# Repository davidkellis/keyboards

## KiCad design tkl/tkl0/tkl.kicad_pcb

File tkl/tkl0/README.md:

# TKL v0: original KiCad project

This is the original keyboard project that preceded the later numbered design
iterations. Its PCB, schematic, and project files are preserved byte for byte.

- Open [tkl.kicad_pro](tkl.kicad_pro) in KiCad.
- [PCB](tkl.kicad_pcb)
- [Schematic](tkl.kicad_sch)

The KiCad project is still named `tkl`; the directory name identifies this
snapshot as v0. See the [repository index](../../README.md) for later revisions.

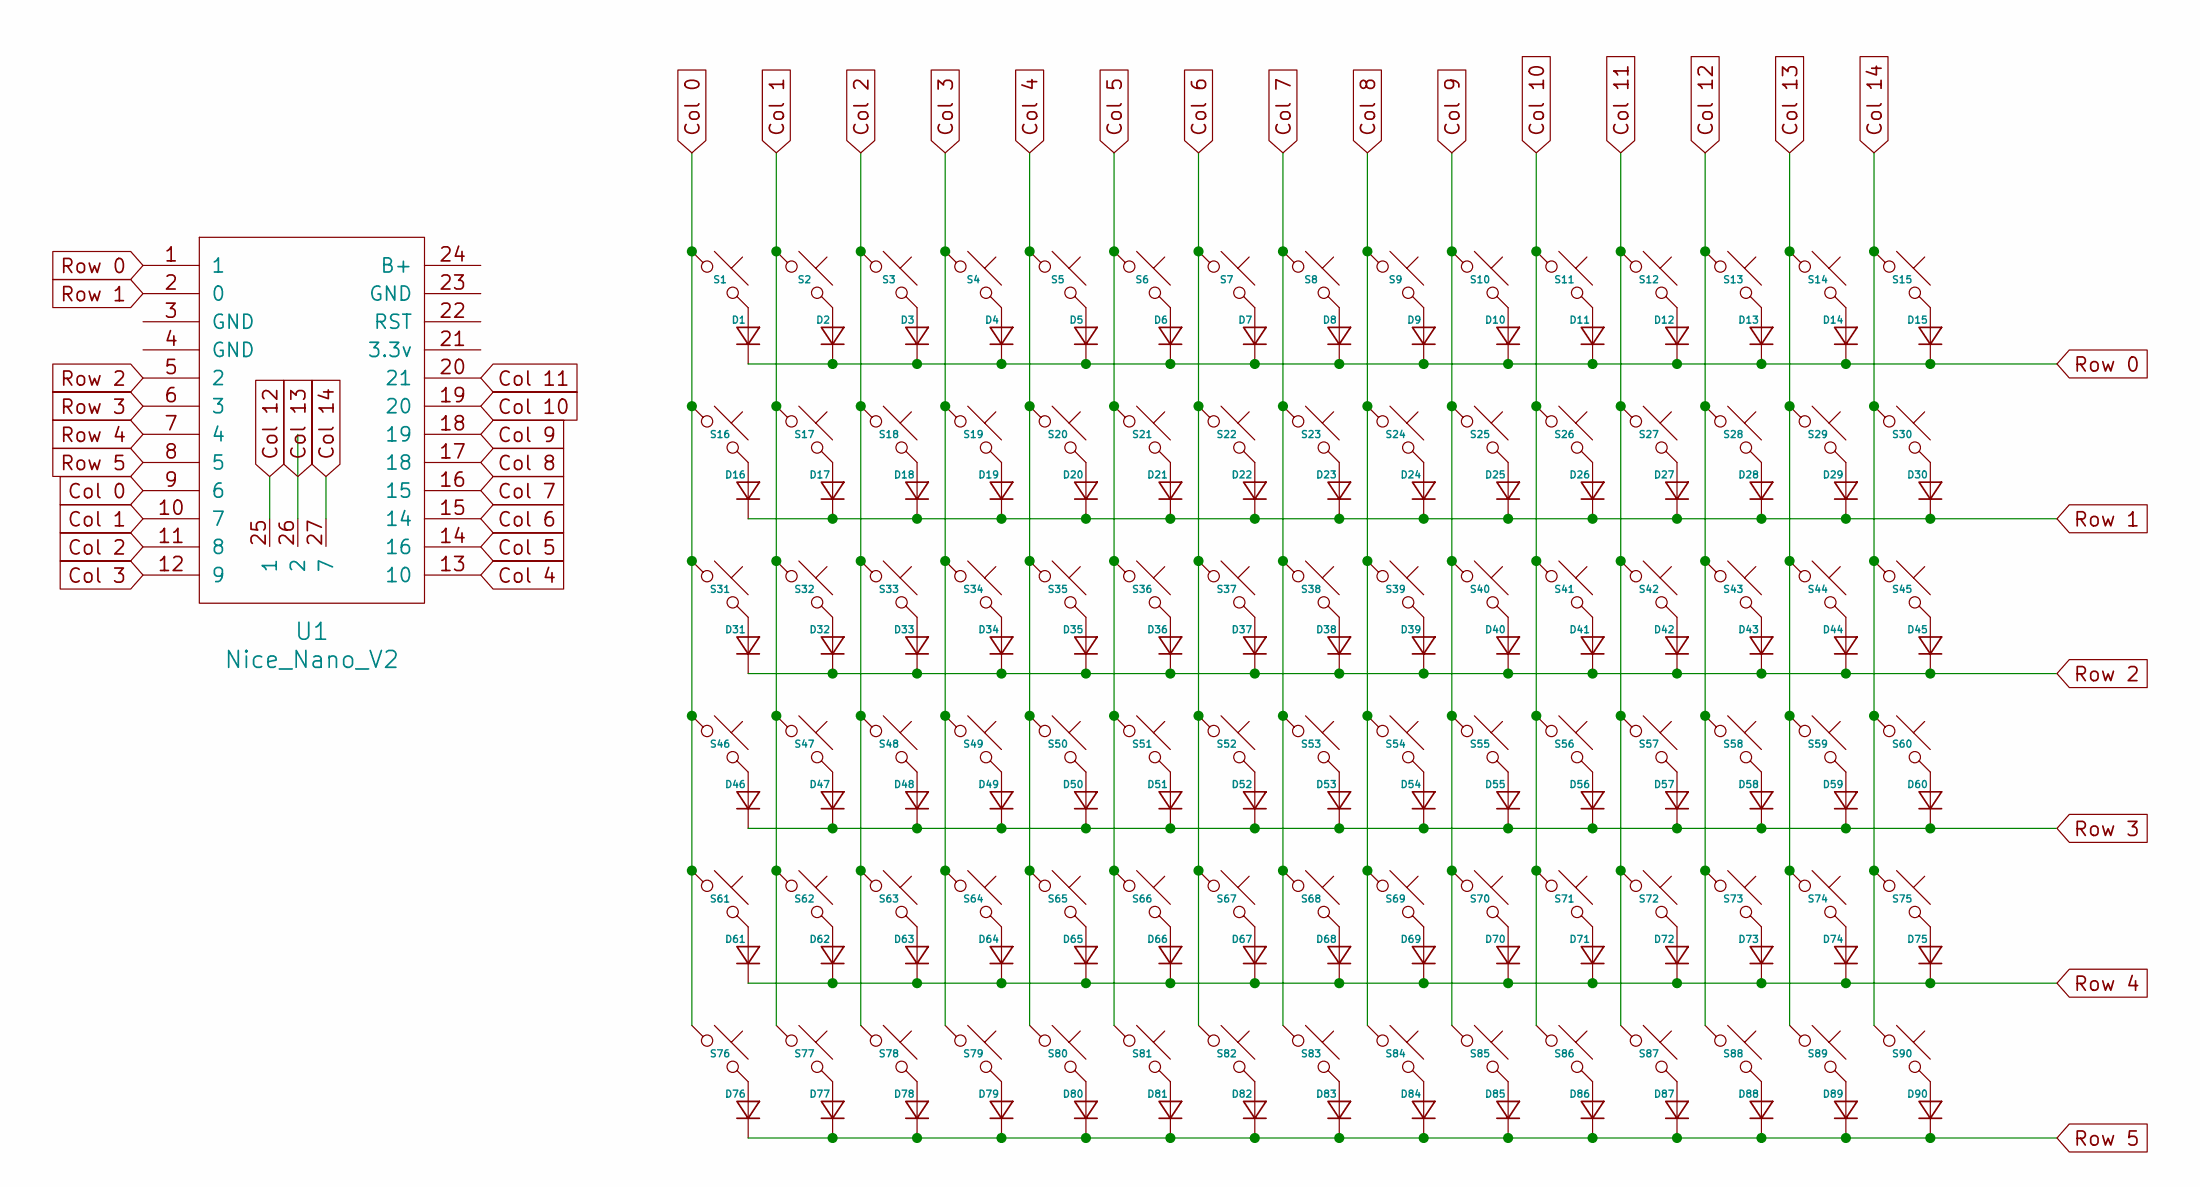
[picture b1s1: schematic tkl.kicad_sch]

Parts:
D1, D2, D3, D4, D5, D6, D7, D8, D9, D10, D11, D12, D13, D14, D15, D16, D17, D18, D19, D20, D21, D22, D23, D24, D25, D26, D27, D28, D29, D30, D31, D32, D33, D34, D35, D36, D37, D38, D39, D40, D41, D42, D43, D44, D45, D46, D47, D48, D49, D50, D51, D52, D53, D54, D55, D56, D57, D58, D59, D60, D61, D62, D63, D64, D65, D66, D67, D68, D69, D70, D71, D72, D73, D74, D75, D76, D77, D78, D79, D80, D81, D82, D83, D84, D85, D86, D87, D88, D89, D90: Diode_DO-35
S1, S2, S3, S4, S5, S6, S7, S8, S9, S10, S11, S12, S13, S14, S15, S16, S17, S18, S19, S20, S21, S22, S23, S24, S25, S26, S27, S28, S29, S30, S31, S32, S33, S34, S35, S36, S37, S38, S39, S40, S41, S42, S43, S44, S45, S46, S47, S48, S49, S50, S51, S52, S53, S54, S55, S56, S57, S58, S59, S60, S61, S62, S63, S64, S65, S66, S67, S68, S69, S70, S71, S72, S73, S74, S75, S76, S77, S78, S79, S80, S81, S82, S83, S84, S85, S86, S87, S88, S89, S90: Choc_V2_1.00u
U1: Nice_Nano_V2

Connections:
Col 0: S1.1, S16.1, S31.1, S46.1, S61.1, S76.1, U1.9 (6)
Col 1: S2.1, S17.1, S32.1, S47.1, S62.1, S77.1, U1.10 (7)
Col 2: S3.1, S18.1, S33.1, S48.1, S63.1, S78.1, U1.11 (8)
Col 3: S4.1, S19.1, S34.1, S49.1, S64.1, S79.1, U1.12 (9)
Col 4: S5.1, S20.1, S35.1, S50.1, S65.1, S80.1, U1.13 (10)
Col 5: S6.1, S21.1, S36.1, S51.1, S66.1, S81.1, U1.14 (16)
Col 6: S7.1, S22.1, S37.1, S52.1, S67.1, S82.1, U1.15 (14)
Col 7: S8.1, S23.1, S38.1, S53.1, S68.1, S83.1, U1.16 (15)
Col 8: S9.1, S24.1, S39.1, S54.1, S69.1, S84.1, U1.17 (18)
Col 9: S10.1, S25.1, S40.1, S55.1, S70.1, S85.1, U1.18 (19)
Col 10: S11.1, S26.1, S41.1, S56.1, S71.1, S86.1, U1.19 (20)
Col 11: S12.1, S27.1, S42.1, S57.1, S72.1, S87.1, U1.20 (21)
Col 12: S13.1, S28.1, S43.1, S58.1, S73.1, S88.1, U1.25 (1)
Col 13: S14.1, S29.1, S44.1, S59.1, S74.1, S89.1, U1.26 (2)
Col 14: S15.1, S30.1, S45.1, S60.1, S75.1, S90.1, U1.27 (7)
unnamed: D1.2 (A), S1.2
unnamed: D2.2 (A), S2.2
unnamed: D3.2 (A), S3.2
unnamed: D4.2 (A), S4.2
unnamed: D5.2 (A), S5.2
unnamed: D6.2 (A), S6.2
unnamed: D7.2 (A), S7.2
unnamed: D8.2 (A), S8.2
unnamed: D9.2 (A), S9.2
unnamed: D10.2 (A), S10.2
unnamed: D11.2 (A), S11.2
unnamed: D12.2 (A), S12.2
unnamed: D13.2 (A), S13.2
unnamed: D14.2 (A), S14.2
unnamed: D15.2 (A), S15.2
unnamed: D16.2 (A), S16.2
unnamed: D17.2 (A), S17.2
unnamed: D18.2 (A), S18.2
unnamed: D19.2 (A), S19.2
unnamed: D20.2 (A), S20.2
unnamed: D21.2 (A), S21.2
unnamed: D22.2 (A), S22.2
unnamed: D23.2 (A), S23.2
unnamed: D24.2 (A), S24.2
unnamed: D25.2 (A), S25.2
unnamed: D26.2 (A), S26.2
unnamed: D27.2 (A), S27.2
unnamed: D28.2 (A), S28.2
unnamed: D29.2 (A), S29.2
unnamed: D30.2 (A), S30.2
unnamed: D31.2 (A), S31.2
unnamed: D32.2 (A), S32.2
unnamed: D33.2 (A), S33.2
unnamed: D34.2 (A), S34.2
unnamed: D35.2 (A), S35.2
unnamed: D36.2 (A), S36.2
unnamed: D37.2 (A), S37.2
unnamed: D38.2 (A), S38.2
unnamed: D39.2 (A), S39.2
unnamed: D40.2 (A), S40.2
unnamed: D41.2 (A), S41.2
unnamed: D42.2 (A), S42.2
unnamed: D43.2 (A), S43.2
unnamed: D44.2 (A), S44.2
unnamed: D45.2 (A), S45.2
unnamed: D46.2 (A), S46.2
unnamed: D47.2 (A), S47.2
unnamed: D48.2 (A), S48.2
unnamed: D49.2 (A), S49.2
unnamed: D50.2 (A), S50.2
unnamed: D51.2 (A), S51.2
unnamed: D52.2 (A), S52.2
unnamed: D53.2 (A), S53.2
unnamed: D54.2 (A), S54.2
unnamed: D55.2 (A), S55.2
unnamed: D56.2 (A), S56.2
unnamed: D57.2 (A), S57.2
unnamed: D58.2 (A), S58.2
unnamed: D59.2 (A), S59.2
unnamed: D60.2 (A), S60.2
unnamed: D61.2 (A), S61.2
unnamed: D62.2 (A), S62.2
unnamed: D63.2 (A), S63.2
unnamed: D64.2 (A), S64.2
unnamed: D65.2 (A), S65.2
unnamed: D66.2 (A), S66.2
unnamed: D67.2 (A), S67.2
unnamed: D68.2 (A), S68.2
unnamed: D69.2 (A), S69.2
unnamed: D70.2 (A), S70.2
unnamed: D71.2 (A), S71.2
unnamed: D72.2 (A), S72.2
unnamed: D73.2 (A), S73.2
unnamed: D74.2 (A), S74.2
unnamed: D75.2 (A), S75.2
unnamed: D76.2 (A), S76.2
unnamed: D77.2 (A), S77.2
unnamed: D78.2 (A), S78.2
unnamed: D79.2 (A), S79.2
unnamed: D80.2 (A), S80.2
unnamed: D81.2 (A), S81.2
unnamed: D82.2 (A), S82.2
unnamed: D83.2 (A), S83.2
unnamed: D84.2 (A), S84.2
unnamed: D85.2 (A), S85.2
unnamed: D86.2 (A), S86.2
unnamed: D87.2 (A), S87.2
unnamed: D88.2 (A), S88.2
unnamed: D89.2 (A), S89.2
unnamed: D90.2 (A), S90.2
Row 0: D1.1 (K), D2.1 (K), D3.1 (K), D4.1 (K), D5.1 (K), D6.1 (K), D7.1 (K), D8.1 (K), D9.1 (K), D10.1 (K), D11.1 (K), D12.1 (K), D13.1 (K), D14.1 (K), D15.1 (K), U1.1
Row 1: D16.1 (K), D17.1 (K), D18.1 (K), D19.1 (K), D20.1 (K), D21.1 (K), D22.1 (K), D23.1 (K), D24.1 (K), D25.1 (K), D26.1 (K), D27.1 (K), D28.1 (K), D29.1 (K), D30.1 (K), U1.2 (0)
Row 2: D31.1 (K), D32.1 (K), D33.1 (K), D34.1 (K), D35.1 (K), D36.1 (K), D37.1 (K), D38.1 (K), D39.1 (K), D40.1 (K), D41.1 (K), D42.1 (K), D43.1 (K), D44.1 (K), D45.1 (K), U1.5 (2)
Row 3: D46.1 (K), D47.1 (K), D48.1 (K), D49.1 (K), D50.1 (K), D51.1 (K), D52.1 (K), D53.1 (K), D54.1 (K), D55.1 (K), D56.1 (K), D57.1 (K), D58.1 (K), D59.1 (K), D60.1 (K), U1.6 (3)
Row 4: D61.1 (K), D62.1 (K), D63.1 (K), D64.1 (K), D65.1 (K), D66.1 (K), D67.1 (K), D68.1 (K), D69.1 (K), D70.1 (K), D71.1 (K), D72.1 (K), D73.1 (K), D74.1 (K), D75.1 (K), U1.7 (4)
Row 5: D76.1 (K), D77.1 (K), D78.1 (K), D79.1 (K), D80.1 (K), D81.1 (K), D82.1 (K), D83.1 (K), D84.1 (K), D85.1 (K), D86.1 (K), D87.1 (K), D88.1 (K), D89.1 (K), D90.1 (K), U1.8 (5)

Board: 2 copper layers, 181 parts (0 on the bottom side), 111 nets, no tracks yet.

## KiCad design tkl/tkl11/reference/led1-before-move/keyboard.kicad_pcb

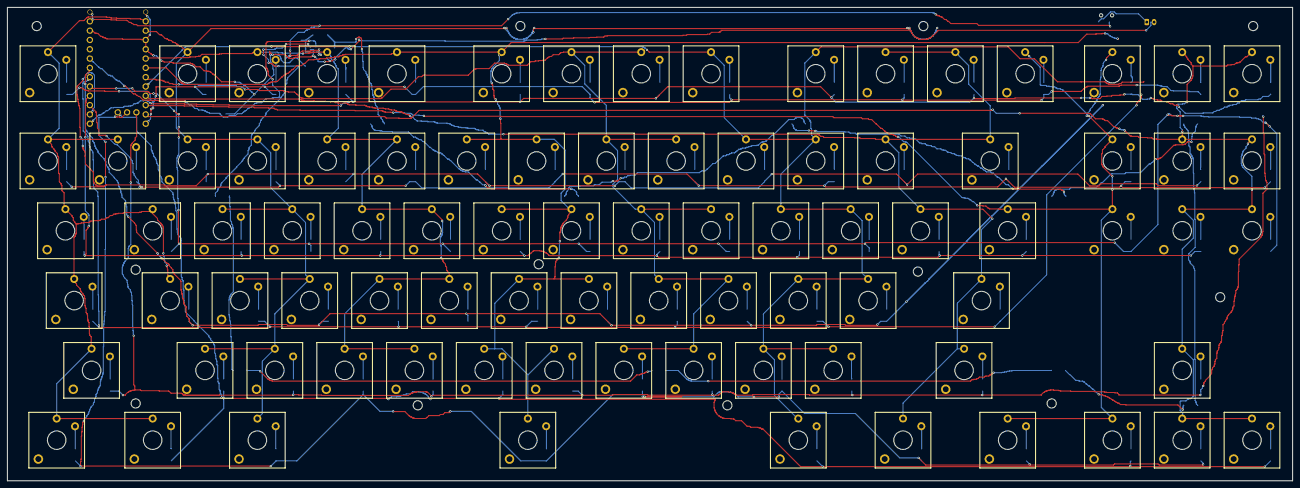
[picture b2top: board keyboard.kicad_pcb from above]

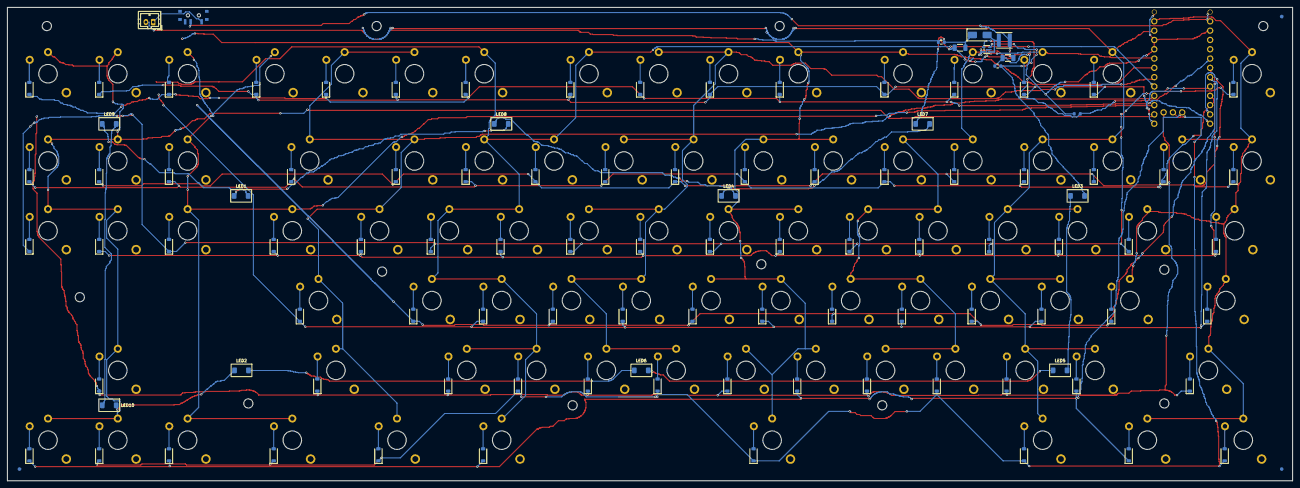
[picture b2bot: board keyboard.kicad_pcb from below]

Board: 2 copper layers, 350.8 x 129.2 mm, 208 parts (110 on the bottom side), 122 nets.

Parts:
C1, C2: 4.7uF 50V; C_1206_3216Metric
D1, D2, D3, D4, D5, D6, D7, D8, D9, D10, D11, D12, D13, D14, D15, D16, D17, D18, D19, D20, D21, D22, D23, D24, D25, D26, D27, D28, D29, D30, D31, D32, D33, D34, D35, D36, D37, D38, D39, D40, D41, D42, D43, D44, D45, D46, D47, D48, D49, D50, D51, D52, D53, D54, D55, D56, D57, D58, D59, D60, D61, D62, D63, D64, D65, D66, D67, D68, D69, D70, D71, D72, D73, D74, D75, D76, D77, D78, D79, D80, D81, D82, D83, D84, D85, D86: BAT46W; D_SOD-123
D87: SS16; D_SMA
FID1, FID2, FID3: Fiducial; Fiducial_1mm_Mask2mm
H1, H2, H3, H4, H5, H6, H7, H8, H9, H10, H11, H12: Mount_M2_2.5mm
J1: B2B-PH-K-S(LF)(SN); J1_JST_PH_B2B-PH-K_1x02_P2.00mm_Vertical
L1: 10uH; L_Sunlord_SWPA4018S
LED1, LED7, LED8, LED9, LED10: LTW-C230DS; LED1_LTW-C230DS_ReverseMount_Hole2.1x2.8
LED2: LTW-C230DS; LED2_LTW-C230DS_ReverseMount_Hole2.1x2.8
LED3: LTW-C230DS; LED3_LTW-C230DS_ReverseMount_Hole2.1x2.8
LED4: LTW-C230DS; LED4_LTW-C230DS_ReverseMount_Hole2.1x2.8
LED5: LTW-C230DS; LED5_LTW-C230DS_ReverseMount_Hole2.1x2.8
LED6: LTW-C230DS; LED6_LTW-C230DS_ReverseMount_Hole2.1x2.8
R9: 1M; R9_R_0603
R10: 100; R_0603_1608Metric
R11: 1M; R_0603_1608Metric
SW1, SW2, SW3, SW4, SW5, SW6, SW7, SW8, SW9, SW10, SW11, SW12, SW13, SW14, SW15, SW16, SW17, SW18, SW19, SW20, SW21, SW22, SW23, SW24, SW25, SW26, SW27, SW28, SW29, SW30, SW32, SW33, SW35, SW36, SW37, SW38, SW39, SW40, SW43, SW44, SW45, SW46, SW47, SW48, SW52, SW53, SW54, SW55, SW56, SW58, SW59, SW60, SW61, SW62, SW63, SW65, SW66, SW67, SW68, SW69, SW71, SW72, SW73, SW74, SW75, SW76, SW82, SW85, SW86: SW_Push; SW_Kailh_Choc_V2_1.00u
SW31: SW_Push; SW_Kailh_Choc_V2_2.00u
SW34, SW41, SW78, SW80, SW81, SW83, SW84: SW_Push; SW_Kailh_Choc_V2_1.50u
SW42: SW_Push; SW42_SW_Kailh_Choc_V2_1.00u
SW49: SW_Push; SW49_SW_Kailh_Choc_V2_1.00u
SW50: SW_Push; SW50_SW_Kailh_Choc_V2_1.00u
SW51: SW_Push; SW_Kailh_Choc_V2_1.75u
SW57, SW64: SW_Push; SW_Kailh_Choc_V2_2.25u
SW70: SW_Push; SW_Kailh_Choc_V2_2.75u
SW77: SW_Push; SW_Kailh_Choc_V2_1.25u
SW79: SW_Push; SW_Kailh_Choc_V2_6.25u
SW87: PCM12SMTR; SW87_SW_SPDT_PCM12
U1: Nice_Nano_V2; U1_Nice_Nano_V2
U2: TPS61169DCKR; SOT-353_SC-70-5

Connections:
BAT_SW: C1.1, L1.1, SW87.2, U1.24 (B+), U1.29 (B+), U2.5
BL_EN: R9.1, U1.20 (21), U2.4
BOOST_SW: D87.2, L1.2, U2.1
COL0: SW1.1, SW17.1, SW25.1, SW34.1, SW43.1, SW51.1, SW58.1, SW64.1, SW77.1, SW83.1, U1.1
COL1: SW2.1, SW18.1, SW26.1, SW35.1, SW44.1, SW52.1, SW59.1, SW65.1, SW71.1, SW78.1, U1.2 (0)
COL2: SW3.1, SW10.1, SW19.1, SW27.1, SW36.1, SW45.1, SW53.1, SW60.1, SW66.1, SW72.1, U1.5 (2)
COL3: SW4.1, SW11.1, SW20.1, SW28.1, SW37.1, SW46.1, SW54.1, SW61.1, SW67.1, SW73.1, SW79.1, U1.6 (3)
COL4: SW5.1, SW12.1, SW21.1, SW29.1, SW38.1, SW47.1, SW55.1, SW62.1, SW68.1, SW74.1, U1.7 (4)
COL5: SW6.1, SW13.1, SW22.1, SW30.1, SW39.1, SW48.1, SW56.1, SW63.1, SW69.1, SW75.1, SW84.1, U1.8 (5)
COL6: SW7.1, SW14.1, SW23.1, SW31.1, SW40.1, SW57.1, SW70.1, SW80.1, U1.9 (6)
COL7: SW8.1, SW15.1, SW32.1, SW41.1, SW49.1, SW81.1, SW85.1, U1.10 (7)
COL8: SW9.1, SW16.1, SW24.1, SW33.1, SW42.1, SW50.1, SW76.1, SW82.1, SW86.1, U1.11 (8)
GND: C1.2, C2.2, J1.2, R9.2, R10.2, R11.2, U1.3 (GND), U1.4 (GND), U1.23 (GND), U1.28 (B-), U2.2
LED_FB: LED3.1, R10.1, U2.3
LED_HV: C2.1, D87.1, LED7.2, R11.1
LED_LINK_1: LED4.2, LED7.1
LED_LINK_2: LED4.1, LED8.2
LED_LINK_3: LED1.2, LED8.1
LED_LINK_4: LED1.1, LED9.2
LED_LINK_5: LED9.1, LED10.2
LED_LINK_6: LED2.2, LED10.1
LED_LINK_7: LED2.1, LED6.2
LED_LINK_8: LED5.2, LED6.1
LED_LINK_9: LED3.2, LED5.1
unnamed: D1.2, SW1.2
unnamed: D2.2, SW2.2
unnamed: D3.2, SW3.2
unnamed: D4.2, SW4.2
unnamed: D5.2, SW5.2
unnamed: D6.2, SW6.2
unnamed: D7.2, SW7.2
unnamed: D8.2, SW8.2
unnamed: D9.2, SW9.2
unnamed: D10.2, SW10.2
unnamed: D11.2, SW11.2
unnamed: D12.2, SW12.2
unnamed: D13.2, SW13.2
unnamed: D14.2, SW14.2
unnamed: D15.2, SW15.2
unnamed: D16.2, SW16.2
unnamed: D17.2, SW17.2
unnamed: D18.2, SW18.2
unnamed: D19.2, SW19.2
unnamed: D20.2, SW20.2
unnamed: D21.2, SW21.2
unnamed: D22.2, SW22.2
unnamed: D23.2, SW23.2
unnamed: D24.2, SW24.2
unnamed: D25.2, SW25.2
unnamed: D26.2, SW26.2
unnamed: D27.2, SW27.2
unnamed: D28.2, SW28.2
unnamed: D29.2, SW29.2
unnamed: D30.2, SW30.2
unnamed: D31.2, SW31.2
unnamed: D32.2, SW32.2
unnamed: D33.2, SW33.2
unnamed: D34.2, SW34.2
unnamed: D35.2, SW35.2
unnamed: D36.2, SW36.2
unnamed: D37.2, SW37.2
unnamed: D38.2, SW38.2
unnamed: D39.2, SW39.2
unnamed: D40.2, SW40.2
unnamed: D41.2, SW41.2
unnamed: D42.2, SW42.2
unnamed: D43.2, SW43.2
unnamed: D44.2, SW44.2
unnamed: D45.2, SW45.2
unnamed: D46.2, SW46.2
unnamed: D47.2, SW47.2
unnamed: D48.2, SW48.2
unnamed: D49.2, SW49.2
unnamed: D50.2, SW50.2
unnamed: D51.2, SW51.2
unnamed: D52.2, SW52.2
unnamed: D53.2, SW53.2
unnamed: D54.2, SW54.2
unnamed: D55.2, SW55.2
unnamed: D56.2, SW56.2
unnamed: D57.2, SW57.2
unnamed: D58.2, SW58.2
unnamed: D59.2, SW59.2
unnamed: D60.2, SW60.2
unnamed: D61.2, SW61.2
unnamed: D62.2, SW62.2
unnamed: D63.2, SW63.2
unnamed: D64.2, SW64.2
unnamed: D65.2, SW65.2
unnamed: D66.2, SW66.2
unnamed: D67.2, SW67.2
unnamed: D68.2, SW68.2
unnamed: D69.2, SW69.2
unnamed: D70.2, SW70.2
unnamed: D71.2, SW71.2
unnamed: D72.2, SW72.2
unnamed: D73.2, SW73.2
unnamed: D74.2, SW74.2
unnamed: D75.2, SW75.2
unnamed: D76.2, SW76.2
unnamed: D77.2, SW77.2
unnamed: D78.2, SW78.2
unnamed: D79.2, SW79.2
unnamed: D80.2, SW80.2
unnamed: D81.2, SW81.2
unnamed: D82.2, SW82.2
unnamed: D83.2, SW83.2
unnamed: D84.2, SW84.2
unnamed: D85.2, SW85.2
unnamed: D86.2, SW86.2
ROW0: D1.1, D2.1, D3.1, D4.1, D5.1, D6.1, D7.1, D8.1, D9.1, U1.12 (9)
ROW1: D10.1, D11.1, D12.1, D13.1, D14.1, D15.1, D16.1, U1.13 (10)
ROW2: D17.1, D18.1, D19.1, D20.1, D21.1, D22.1, D23.1, D24.1, U1.14 (16)
ROW3: D25.1, D26.1, D27.1, D28.1, D29.1, D30.1, D31.1, D32.1, D33.1, U1.15 (14)
ROW4: D34.1, D35.1, D36.1, D37.1, D38.1, D39.1, D40.1, D41.1, D42.1, U1.16 (15)
ROW5: D43.1, D44.1, D45.1, D46.1, D47.1, D48.1, D49.1, D50.1, U1.17 (18)
ROW6: D51.1, D52.1, D53.1, D54.1, D55.1, D56.1, D57.1, U1.18 (19)
ROW7: D58.1, D59.1, D60.1, D61.1, D62.1, D63.1, U1.19 (20)
ROW9: D64.1, D70.1, D71.1, D72.1, D73.1, D74.1, D75.1, D76.1, U1.25 (1)
ROW10: D66.1, D68.1, D69.1, D77.1, D78.1, D79.1, D80.1, D81.1, D82.1, U1.26 (2)
ROW11: D65.1, D67.1, D83.1, D84.1, D85.1, D86.1, U1.27 (7)
VBAT: J1.1, SW87.1

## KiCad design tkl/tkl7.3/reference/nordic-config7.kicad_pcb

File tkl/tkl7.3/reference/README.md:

# v7 source material

`nordic-config7.kicad_pcb` is a KiCad 10 import of Nordic Semiconductor's
nRF52840-QIAA reference layout 1.3, configuration 7 (four-component RF match).
The original Altium file was imported with `kicad-cli pcb import --format altium`.
The controller, crystals, decoupling, both DC/DC stages and matching network
are transformed together onto the keyboard underside.

- [Nordic reference layout downloads](https://www.nordicsemi.com/Products/nRF52840/Compatible-downloads)
- [Original reference archive](https://nsscprodmedia.blob.core.windows.net/prod/software-and-other-downloads/reference-layouts/nrf52840/nrf52840-qiaa-reference-layout-1_3.zip)
- [nRF52840 pin assignments](https://docs.nordicsemi.com/r/bundle/ps_nrf52840/page/pin.html)
- [nRF52840 power/regulator limits](https://docs.nordicsemi.com/r/bundle/ps_nrf52840/page/power.html)
- [TI BQ24072 datasheet](https://www.ti.com/lit/ds/symlink/bq24072.pdf)
- [Lite-On reverse LED dimensions and polarity](https://docs.rs-online.com/6872/0900766b80e28fac.pdf)
- [BAT46W low-drop matrix diode](https://www.diodes.com/datasheet/download/BAT46W.pdf)
- [Diodes DMN2056U MOSFET datasheet](https://www.diodes.com/datasheet/download/DMN2056U.pdf)
- [C&K PCM12 switch](https://www.ckswitches.com/media/1424/pcm.pdf)

`matrix-source.kicad_pcb` preserves the checkpoint layout, with routing and
zones removed, as the deterministic input for the placement builder. Its old
controller circuitry is discarded by that builder. It is not a fabrication file.

`mcu-pinmap.json` records physical nRF package pad assignments.
`firmware-pins.json` maps matrix/backlight signals to MCU GPIOs. Logical ROW8
is absent; compact it out when defining an eleven-row ZMK matrix.

Reference modifications: mirror the complete block onto B.Cu, convert local
blind vias to through vias, remove unused GPIO stubs, rename selected GPIO nets,
replace the reference coupon boundary with the keyboard perimeter, and connect
a U.FL receptacle directly at the RF feed endpoint. Keep the imported RF copper
exclusions. Via-in-pad holes require filling, planarization and copper capping;
tenting alone is not suitable under the package lands.

The RF/crystal/regulator copper was also compared geometrically with a fresh
transformed reference placement after routing cleanup. No original copper
was lost on RF, ANT, RF_MATCH, DCC, DCDC_FILTER, DCCH, DEC1, DEC2, DEC3,
DEC4_6, DEC5, DECUSB, XC1 or XC2. The manual USB pair was preserved as well.
This is a geometry check, not an RF simulation or a substitute for prototype
measurements on the actual stackup.

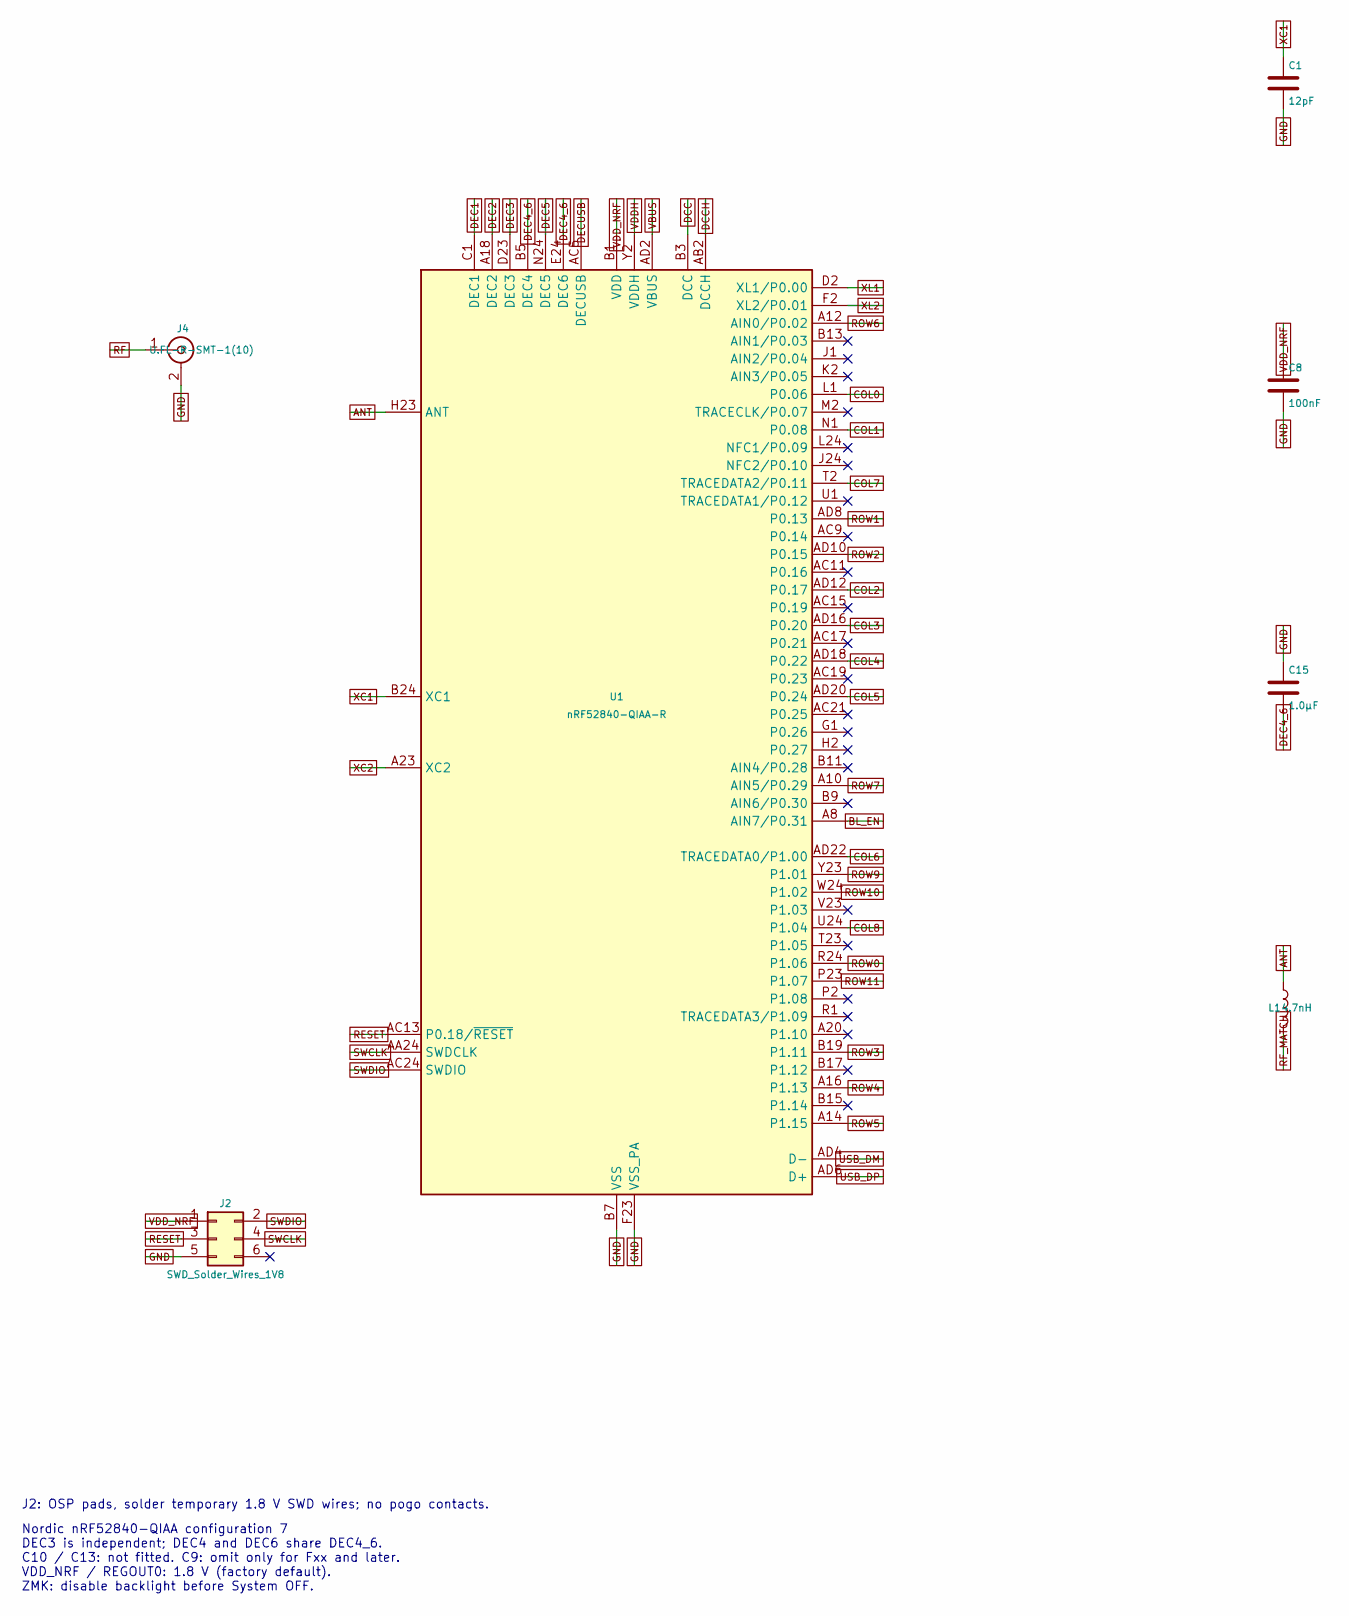
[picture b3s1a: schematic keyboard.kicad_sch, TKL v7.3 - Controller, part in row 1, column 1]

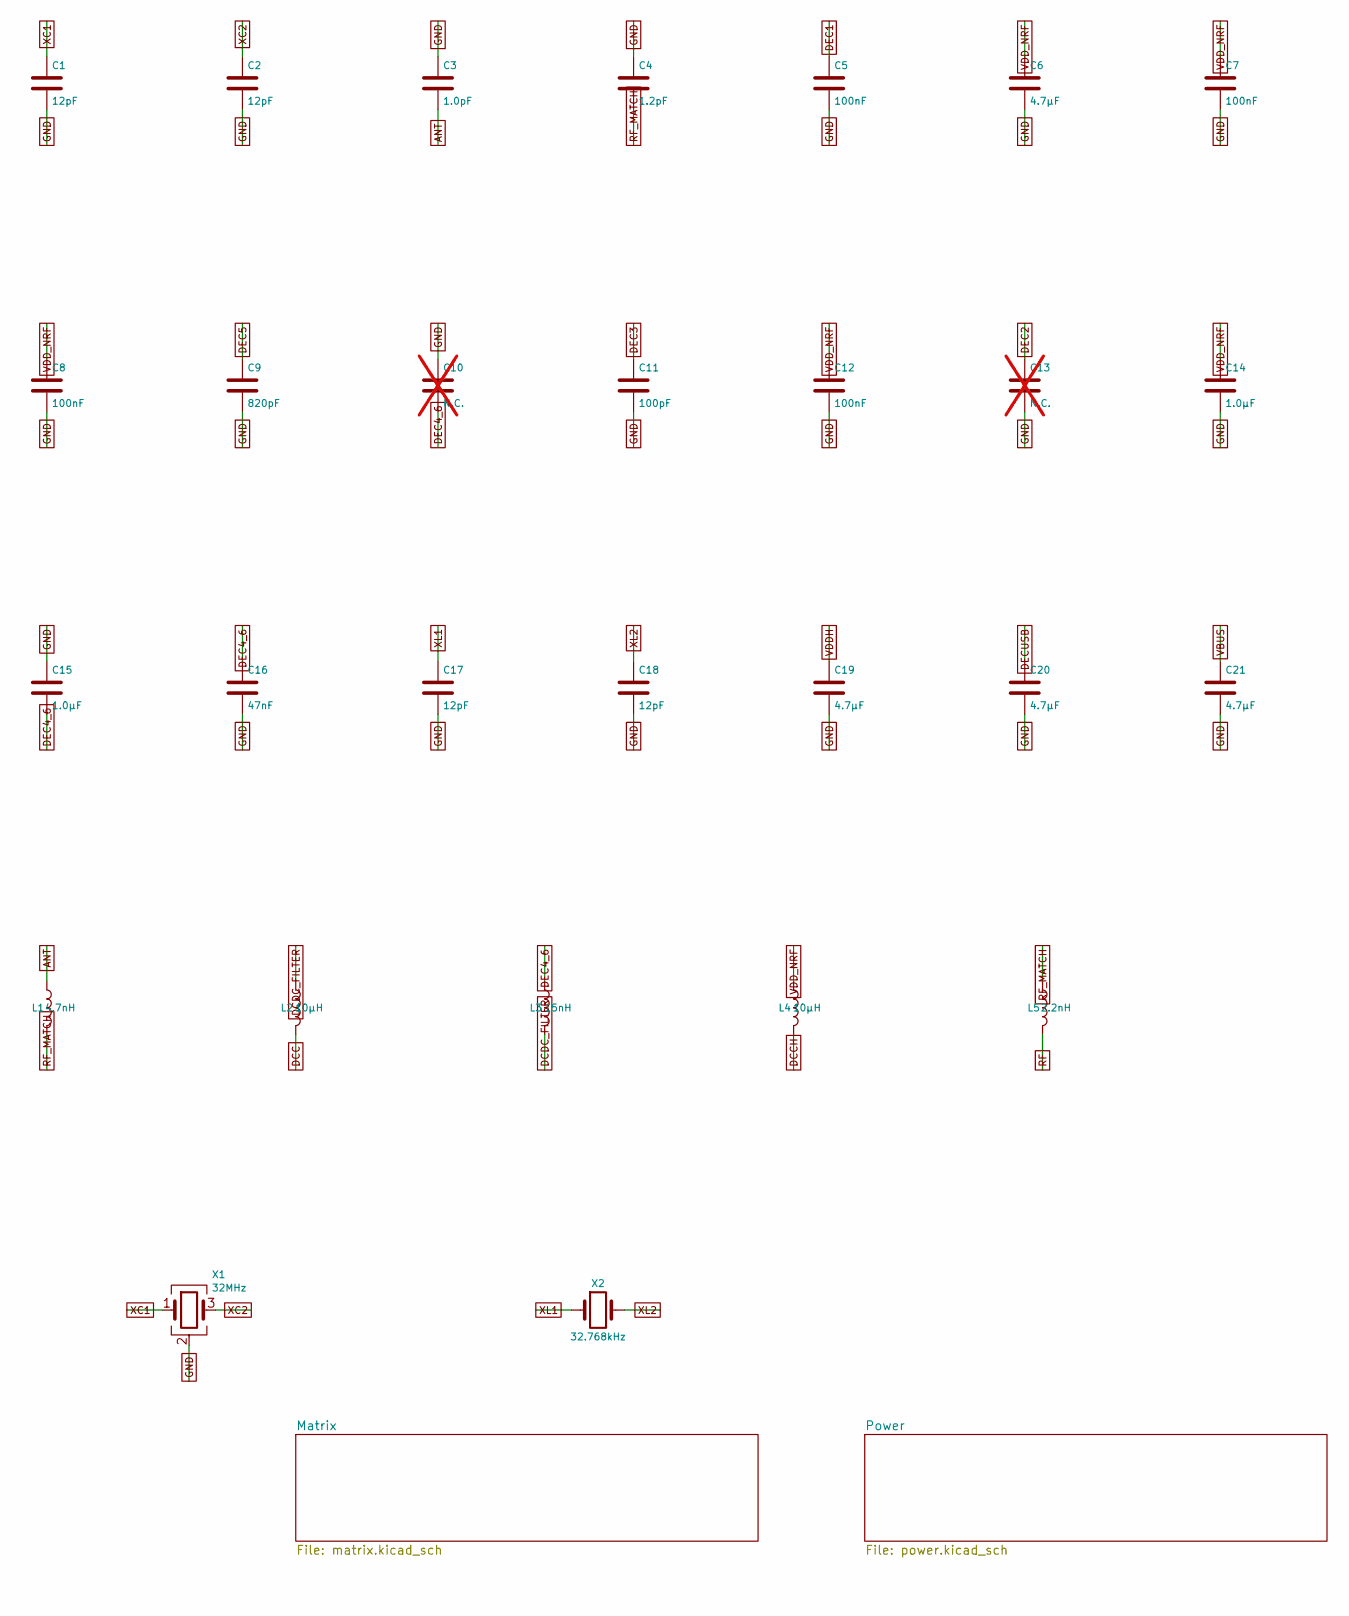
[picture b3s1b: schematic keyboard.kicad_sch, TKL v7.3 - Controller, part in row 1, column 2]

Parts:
C1: 12pF; C1_CAPC1005X04L; MPN GRM1555C1H120GA01D; LCSC C161527
C2: 12pF; C2_CAPC1005X04L; MPN GRM1555C1H120GA01D; LCSC C161527
C3: 1.0pF; C3_CAPC1005X04L; MPN GJM1555C1H1R0WB01D; LCSC C72134
C4: 1.2pF; C4_CAPC1005X04L; MPN GJM1555C1H1R2WB01D; LCSC C76899
C5: 100nF; C5_CAPC1005X04L; MPN CL05B104KO5NNNC; LCSC C1525
C6: 4.7µF; C6_CAPC1608X06L; MPN GRM188Z71A475KE15D; LCSC C913474
C7: 100nF; C7_CAPC1005X04L; MPN CL05B104KO5NNNC; LCSC C1525
C8: 100nF; C8_CAPC1005X04L; MPN CL05B104KO5NNNC; LCSC C1525
C9: 820pF; C9_CAPC1005X04L; MPN GRM1555C1H821JA01D; LCSC C85943
C10: N.C.; C10_CAPC1005X04L; not fitted
C11: 100pF; C11_CAPC1005X04L; MPN GRM1555C1H101JA01D; LCSC C77177
C12: 100nF; C12_CAPC1005X04L; MPN CL05B104KO5NNNC; LCSC C1525
C13: N.C.; C13_CAPC1005X04L; not fitted
C14: 1.0µF; C14_CAPC1608X06L; MPN 0603B105K160CT; LCSC C108463
C15: 1.0µF; C15_CAPC1608X06L; MPN 0603B105K160CT; LCSC C108463
C16: 47nF; C16_CAPC1005X04L; MPN GRM155R71H473KE14D; LCSC C117757
C17: 12pF; C17_CAPC1005X04L; MPN GRM1555C1H120GA01D; LCSC C161527
C18: 12pF; C18_CAPC1005X04L; MPN GRM1555C1H120GA01D; LCSC C161527
C19: 4.7µF; C19_CAPC1608X06L; MPN GRM188Z71A475KE15D; LCSC C913474
C20: 4.7µF; C20_CAPC1608X06L; MPN GRM188Z71A475KE15D; LCSC C913474
C21: 4.7µF; C21_CAPC1608X06L; MPN GRM188Z71A475KE15D; LCSC C913474
J2: SWD_Solder_Wires_1V8; J2_Tag-Connect_TC2030-IDC-NL_2x03_P1.27mm_Vertical
J4: U.FL-R-SMT-1(10); J4_U.FL_Hirose_U.FL-R-SMT-1_Vertical; MPN U.FL-R-SMT-1(10); LCSC C88373
L1: 4.7nH; L1_INDC1005X04L; MPN LQW15AN4N7G80D; LCSC C412337
L2: 10µH; L2_INDC1608X06L; MPN LQM18DN100M70L; LCSC C713281
L3: 15nH; L3_INDC1005X04L; MPN LQG15HN15NJ02D; LCSC C97979
L4: 10µH; L4_INDC1608X06L; MPN LQM18DN100M70L; LCSC C713281
L5: 2.2nH; L5_INDC1005X04L; MPN LQW15AN2N2G80D; LCSC C412264
U1: nRF52840-QIAA-R; U1_AQFN50P700X700X85_HS-74N; MPN NRF52840-QIAA-R; LCSC C190794
X1: 32MHz; X1_BT-XTAL_2016; MPN X201632MKB4SI; LCSC C718072
X2: 32.768kHz; X2_XTAL_3215; MPN FC31M2-32.768-N09LLDT; LCSC C2848222

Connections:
D+: U1.AD6 (D+)
D-: U1.AD4 (D-)
DEC1: C5.1, U1.C1 (DEC1)
DEC3: C11.1, U1.D23 (DEC3)
DEC4_6: C10.2, C15.2, C16.1, L3.1, U1.B5 (DEC4), U1.E24 (DEC6)
GND: C1.2, C2.2, C3.1, C4.1, C5.2, C6.2, C7.2, C8.2, C9.2, C10.1, C11.2, C12.2, C13.2, C14.2, C15.1, C16.2, C17.2, C18.2, C19.2, C20.2, C21.2, J2.5, J4.2 (Ext), U1.74, U1.B7 (VSS), U1.EP (VSS), U1.F23 (VSS_PA), X1.2 (G), X1.4 (G)
NetC3_2: C3.2, L1.1, U1.H23 (ANT)
NetC4_2: C4.2, L1.2, L5.1
NetC9_1: C9.1, U1.N24 (DEC5)
NetC13_1: C13.1, U1.A18 (DEC2)
NetC20_1: C20.1, U1.AC5 (DECUSB)
NetL2_1: L2.1, L3.2
NetL2_2: L2.2, U1.B3 (DCC)
NetL4_2: L4.2, U1.AB2 (DCCH)
P0.00/XL1: C17.1, U1.D2 (XL1/P0.00), X2.1
P0.01/XL2: C18.1, U1.F2 (XL2/P0.01), X2.2
P0.02/AIN0: U1.A12 (AIN0/P0.02)
P0.03/AIN1: U1.B13 (AIN1/P0.03)
P0.04/AIN2: U1.J1 (AIN2/P0.04)
P0.05/AIN3: U1.K2 (AIN3/P0.05)
P0.06: U1.L1 (P0.06)
P0.07: U1.M2 (TRACECLK/P0.07)
P0.08: U1.N1 (P0.08)
P0.09/NFC1: U1.L24 (NFC1/P0.09)
P0.10/NFC2: U1.J24 (NFC2/P0.10)
P0.11: U1.T2 (TRACEDATA2/P0.11)
P0.12: U1.U1 (TRACEDATA1/P0.12)
P0.13: U1.AD8 (P0.13)
P0.14: U1.AC9 (P0.14)
P0.15: U1.AD10 (P0.15)
P0.16: U1.AC11 (P0.16)
P0.17: U1.AD12 (P0.17)
P0.18/RESET: J2.3, U1.AC13 (P0.18/~RESET)
P0.19: U1.AC15 (P0.19)
P0.20: U1.AD16 (P0.20)
P0.21: U1.AC17 (P0.21)
P0.22: U1.AD18 (P0.22)
P0.23: U1.AC19 (P0.23)
P0.24: U1.AD20 (P0.24)
P0.25: U1.AC21 (P0.25)
P0.26: U1.G1 (P0.26)
P0.27: U1.H2 (P0.27)
P0.28/AIN4: U1.B11 (AIN4/P0.28)
P0.29/AIN5: U1.A10 (AIN5/P0.29)
P0.30/AIN6: U1.B9 (AIN6/P0.30)
P0.31/AIN7: U1.A8 (AIN7/P0.31)
P1.00: U1.AD22 (TRACEDATA0/P1.00)
P1.01: U1.Y23 (P1.01)
P1.02: U1.W24 (P1.02)
P1.03: U1.V23 (P1.03)
P1.04: U1.U24 (P1.04)
P1.05: U1.T23 (P1.05)
P1.06: U1.R24 (P1.06)
P1.07: U1.P23 (P1.07)
P1.08: U1.P2 (P1.08)
P1.09: U1.R1 (TRACEDATA3/P1.09)
P1.10: U1.A20 (P1.10)
P1.11: U1.B19 (P1.11)
P1.12: U1.B17 (P1.12)
P1.13: U1.A16 (P1.13)
P1.14: U1.B15 (P1.14)
P1.15: U1.A14 (P1.15)
RF: J4.1 (In), L5.2
SWDCLK: J2.4, U1.AA24 (SWDCLK)
SWDIO: J2.2, U1.AC24 (SWDIO)
VBUS: C21.1, U1.AD2 (VBUS)
VDD_HV: C19.1, U1.Y2 (VDDH)
VDD_NRF: C6.1, C7.1, C8.1, C12.1, C14.1, J2.1, L4.1, U1.A22 (VDD), U1.AD14 (VDD), U1.AD23 (VDD), U1.B1 (VDD), U1.W1 (VDD)
XC1: C1.1, U1.B24 (XC1), X1.1
XC2: C2.1, U1.A23 (XC2), X1.3

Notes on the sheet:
J2: OSP pads, solder temporary 1.8 V SWD wires; no pogo contacts.
Nordic nRF52840-QIAA configuration 7 DEC3 is independent; DEC4 and DEC6 share DEC4_6. C10 / C13: not fitted. C9: omit only for Fxx and later. VDD_NRF / REGOUT0: 1.8 V (factory default). ZMK: disable backlight before System OFF.

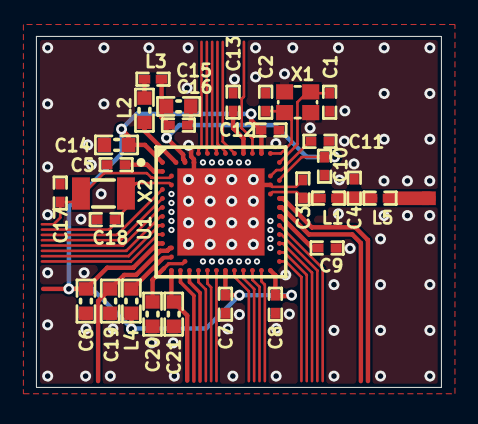
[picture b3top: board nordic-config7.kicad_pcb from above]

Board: 4 copper layers, 22.5 x 19.5 mm, 29 parts (0 on the bottom side), 19 nets.
